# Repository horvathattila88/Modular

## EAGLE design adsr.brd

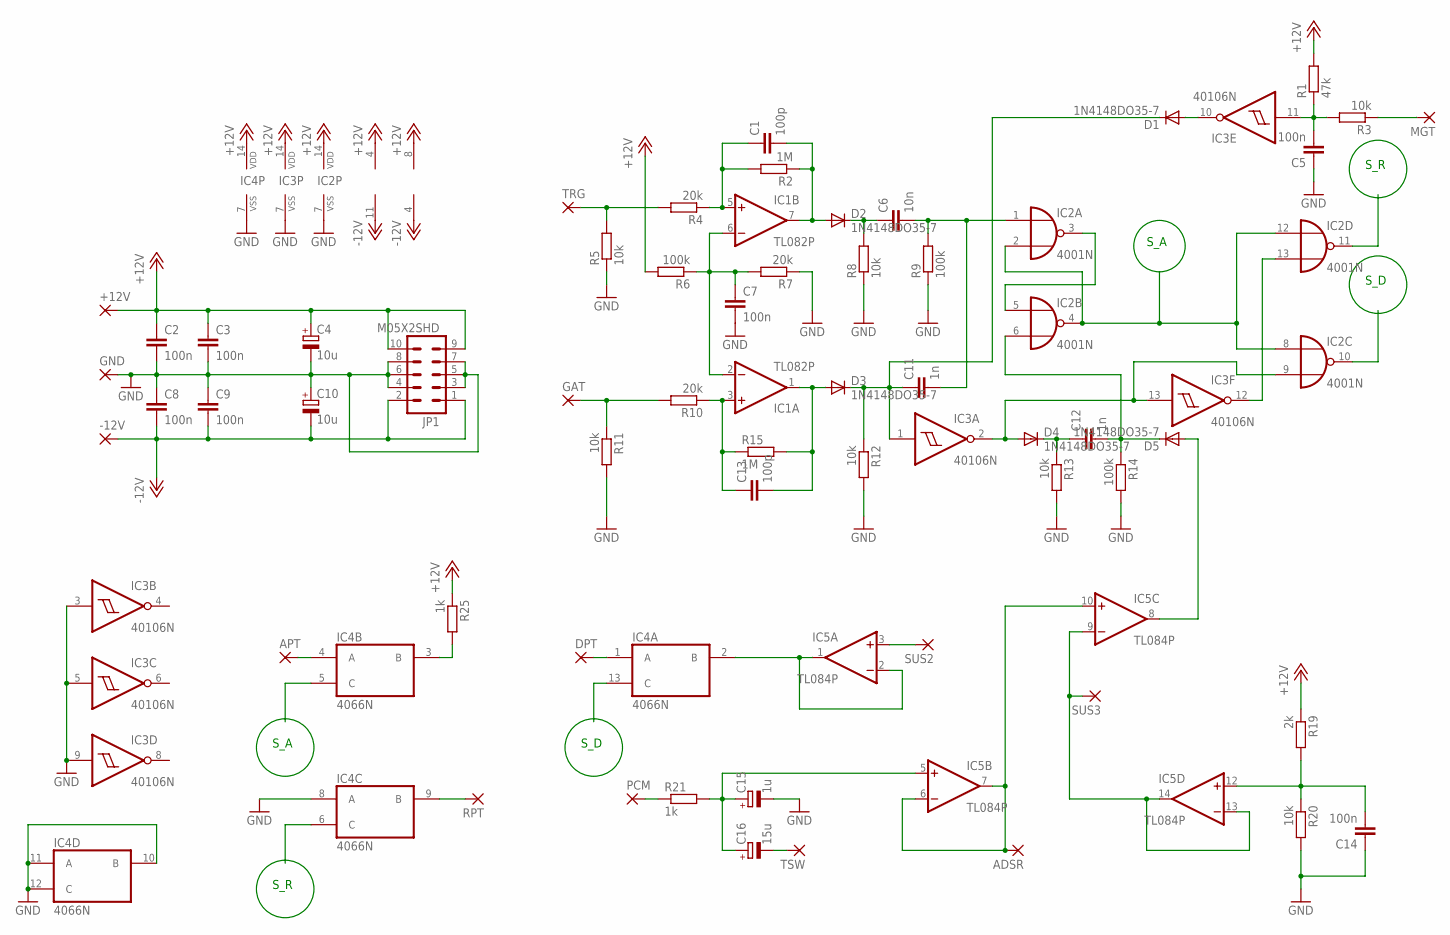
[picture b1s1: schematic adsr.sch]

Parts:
+12V: 2,54/1,0
-12V: 2,54/1,0
ADSR: 2,54/1,0
APT: 2,54/1,0
C1, C13: 100p; C050-035X075
C2, C3, C5, C7, C8, C9, C14: 100n; C050-035X075
C4, C10: 10u; E3,5-8
C6: 10n; C050-035X075
C11, C12: 1n; C050-035X075
C15: 1u; E2,5-6
C16: 15u; E3,5-8
D1, D2, D3, D4, D5: 1N4148DO35-7; DO35-7
DPT: 2,54/1,0
GAT: 2,54/1,0
GND: 2,54/1,0
IC1: TL082P; DIL08
IC2: 4001N; DIL14
IC3: 40106N; DIL14
IC4: 4066N; DIL14
IC5: TL084P; DIL14
JP1: M05X2SHD; 2X5-SHROUDED
MGT: 2,54/1,0
PCM: 2,54/1,0
R1: 47k; 0309/10
R2, R15: 1M; 0309/10
R3, R5, R8, R11, R12, R13, R20: 10k; 0309/10
R4, R7, R10: 20k; 0309/10
R6, R9, R14: 100k; 0309/10
R19: 2k; 0309/10
R21, R25: 1k; 0309/10
RPT: 2,54/1,0
SUS2, SUS3: 2,54/1,0
TRG: 2,54/1,0
TSW: 2,54/1,0

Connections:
+12V: +12V.1, C2.1, C3.1, C4.+, IC1.8 (V+), IC2.14 (VDD), IC3.14 (VDD), IC4.14 (VDD), IC5.4 (V+), JP1.9, JP1.10, R1.2, R6.2, R19.1, R25.1
-12V: -12V.1, C8.2, C9.2, C10.-, IC1.4 (V-), IC5.11 (V-), JP1.1, JP1.2
GND: C2.2, C3.2, C4.-, C5.1, C7.2, C8.1, C9.1, C10.+, C14.1, C15.-, GND.1, IC2.7 (VSS), IC3.3 (I), IC3.5 (I), IC3.7 (VSS), IC3.9 (I), IC4.7 (VSS), IC4.8 (A), IC4.10 (B), IC4.11 (A), IC4.12 (C), JP1.3, JP1.4, JP1.5, JP1.6, JP1.7, JP1.8, R5.1, R7.1, R8.1, R9.1, R11.2, R12.2, R13.2, R14.2, R20.2
unnamed: C1.1, IC1.5 (+IN), R2.2, R4.1
unnamed: R4.2, R5.2, TRG.1
unnamed: C1.2, D2.A, IC1.7 (OUT), R2.1
unnamed: C7.1, IC1.2 (-IN), IC1.6 (-IN), R6.1, R7.2
unnamed: C6.1, D2.C, R8.2
unnamed: C6.2, C11.2, IC2.1 (I0), R9.2
unnamed: C13.2, D3.A, IC1.1 (OUT), R15.2
unnamed: C13.1, IC1.3 (+IN), R10.1, R15.1
unnamed: GAT.1, R10.2, R11.1
unnamed: D4.A, IC2.9 (I1), IC3.2 (O), IC3.13 (I)
unnamed: IC2.3 (O), IC2.5 (I0)
unnamed: C11.1, D1.C, D3.C, IC3.1 (I), R12.1
unnamed: C12.1, D4.C, R13.1
unnamed: C12.2, D5.C, IC2.6 (I1), R14.1
unnamed: D5.A, IC5.8 (OUT)
unnamed: IC2.13 (I1), IC3.12 (O)
unnamed: C5.2, IC3.11 (I), R1.1, R3.2
unnamed: D1.A, IC3.10 (O)
unnamed: MGT.1, R3.1
unnamed: IC5.9 (-IN), IC5.13 (-IN), IC5.14 (OUT), SUS3.1
unnamed: ADSR.1, IC5.6 (-IN), IC5.7 (OUT), IC5.10 (+IN)
unnamed: IC5.3 (+IN), SUS2.1
unnamed: IC4.2 (B), IC5.1 (OUT), IC5.2 (-IN)
unnamed: DPT.1, IC4.1 (A)
unnamed: APT.1, IC4.4 (A)
unnamed: IC4.3 (B), R25.2
unnamed: IC4.9 (B), RPT.1
unnamed: PCM.1, R21.1
unnamed: C16.-, TSW.1
unnamed: C15.+, C16.+, IC5.5 (+IN), R21.2
unnamed: C14.2, IC5.12 (+IN), R19.2, R20.1
S_A: IC2.2 (I1), IC2.4 (O), IC2.8 (I0), IC2.12 (I0), IC4.5 (C)
S_D: IC2.10 (O), IC4.13 (C)
S_R: IC2.11 (O), IC4.6 (C)

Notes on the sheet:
S_A
S_D
S_R

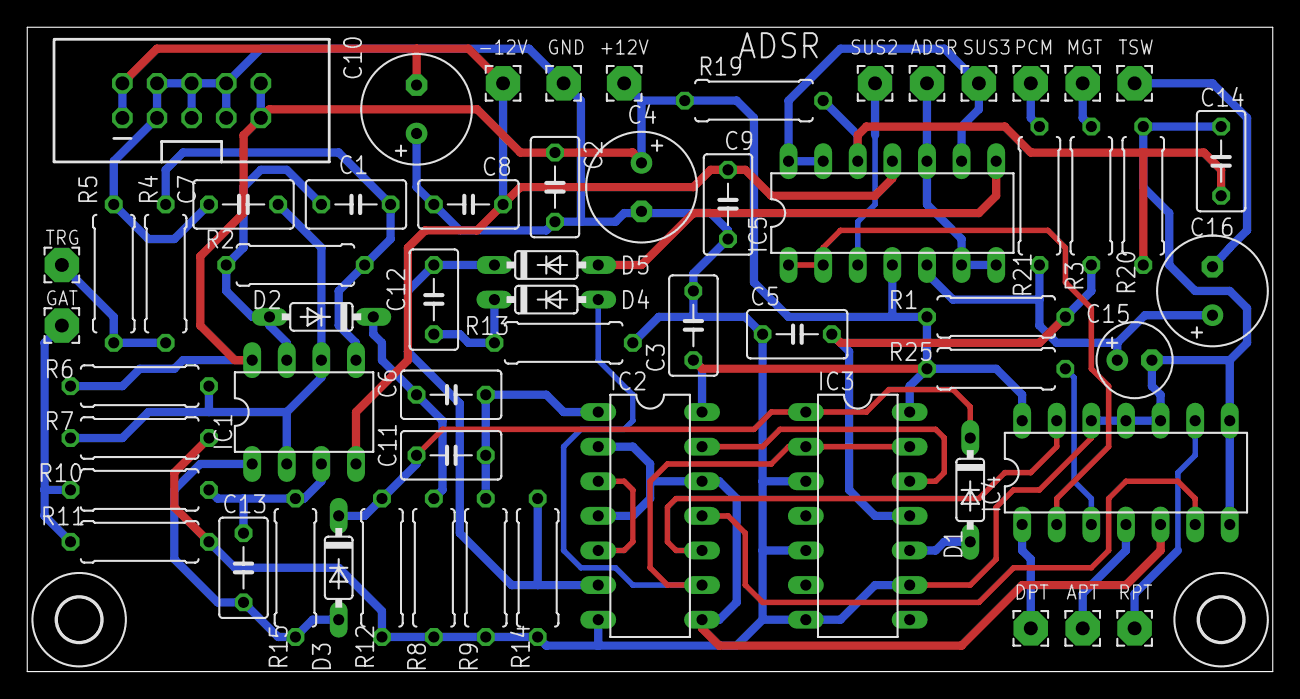
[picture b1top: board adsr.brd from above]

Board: 2 copper layers, 91.4 x 47.3 mm, 62 parts (0 on the bottom side), 37 nets.

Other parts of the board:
U$1, U$2: 3,2

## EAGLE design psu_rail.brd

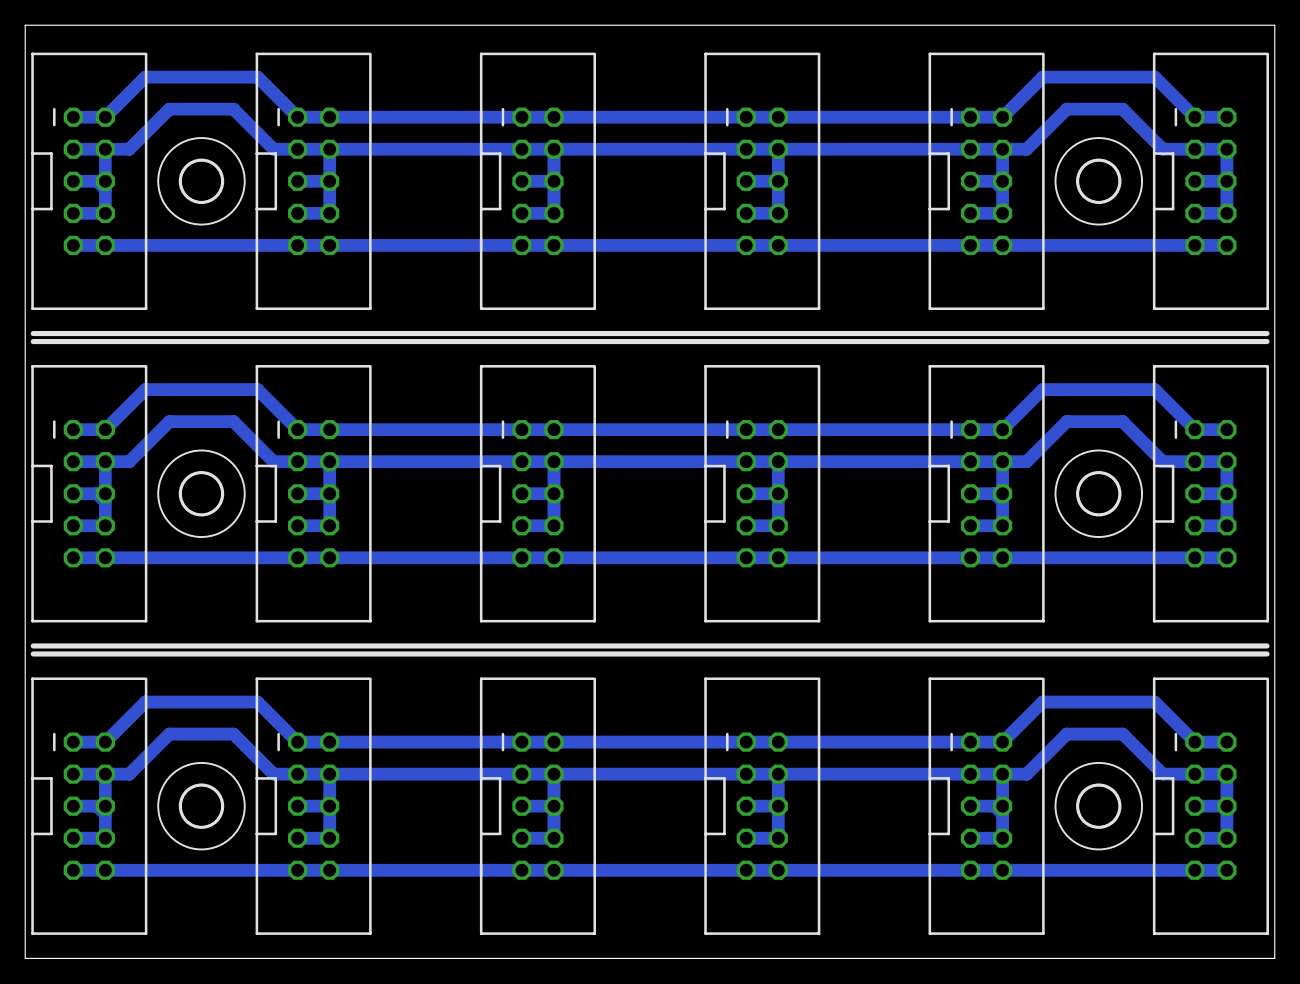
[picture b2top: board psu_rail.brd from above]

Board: 2 copper layers, 99.0 x 74.0 mm, 24 parts (0 on the bottom side), 9 nets.

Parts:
JP1, JP2, JP3, JP4, JP5, JP6, JP7, JP8, JP9, JP10, JP11, JP12, JP13, JP14, JP15, JP16, JP17, JP18: M05X2SHD; 2X5-SHROUDED
U$1, U$2, U$3, U$4, U$6, U$8: 3,2

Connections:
unnamed: JP1.1, JP1.2, JP2.1, JP2.2, JP3.1, JP3.2, JP4.1, JP4.2, JP11.1, JP11.2, JP12.1, JP12.2
unnamed: JP1.9, JP1.10, JP2.9, JP2.10, JP3.9, JP3.10, JP4.9, JP4.10, JP11.9, JP11.10, JP12.9, JP12.10
unnamed: JP1.3, JP1.4, JP1.5, JP1.6, JP1.7, JP1.8, JP2.3, JP2.4, JP2.5, JP2.6, JP2.7, JP2.8, JP3.3, JP3.4, JP3.5, JP3.6, JP3.7, JP3.8, JP4.3, JP4.4, JP4.5, JP4.6, JP4.7, JP4.8, JP11.3, JP11.4, JP11.5, JP11.6, JP11.7, JP11.8, JP12.3, JP12.4, JP12.5, JP12.6, JP12.7, JP12.8
unnamed: JP13.1, JP13.2, JP14.1, JP14.2, JP15.1, JP15.2, JP16.1, JP16.2, JP17.1, JP17.2, JP18.1, JP18.2
unnamed: JP13.9, JP13.10, JP14.9, JP14.10, JP15.9, JP15.10, JP16.9, JP16.10, JP17.9, JP17.10, JP18.9, JP18.10
unnamed: JP13.3, JP13.4, JP13.5, JP13.6, JP13.7, JP13.8, JP14.3, JP14.4, JP14.5, JP14.6, JP14.7, JP14.8, JP15.3, JP15.4, JP15.5, JP15.6, JP15.7, JP15.8, JP16.3, JP16.4, JP16.5, JP16.6, JP16.7, JP16.8, JP17.3, JP17.4, JP17.5, JP17.6, JP17.7, JP17.8, JP18.3, JP18.4, JP18.5, JP18.6, JP18.7, JP18.8
unnamed: JP5.1, JP5.2, JP6.1, JP6.2, JP7.1, JP7.2, JP8.1, JP8.2, JP9.1, JP9.2, JP10.1, JP10.2
unnamed: JP5.9, JP5.10, JP6.9, JP6.10, JP7.9, JP7.10, JP8.9, JP8.10, JP9.9, JP9.10, JP10.9, JP10.10
unnamed: JP5.3, JP5.4, JP5.5, JP5.6, JP5.7, JP5.8, JP6.3, JP6.4, JP6.5, JP6.6, JP6.7, JP6.8, JP7.3, JP7.4, JP7.5, JP7.6, JP7.7, JP7.8, JP8.3, JP8.4, JP8.5, JP8.6, JP8.7, JP8.8, JP9.3, JP9.4, JP9.5, JP9.6, JP9.7, JP9.8, JP10.3, JP10.4, JP10.5, JP10.6, JP10.7, JP10.8

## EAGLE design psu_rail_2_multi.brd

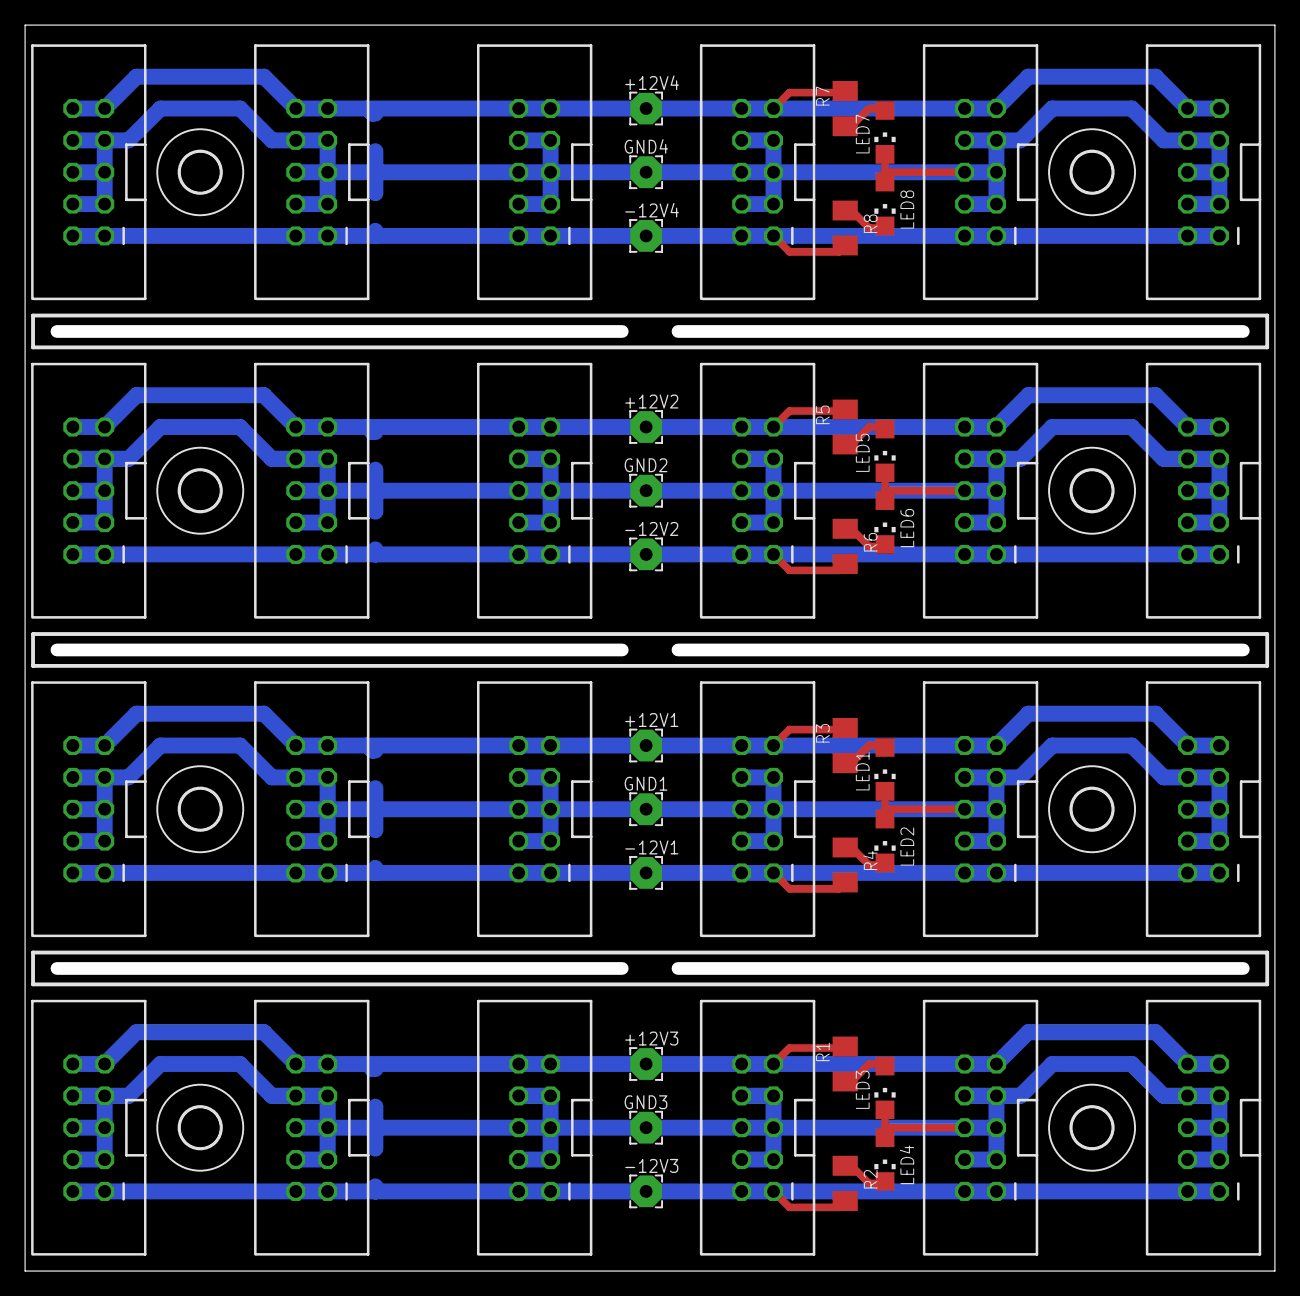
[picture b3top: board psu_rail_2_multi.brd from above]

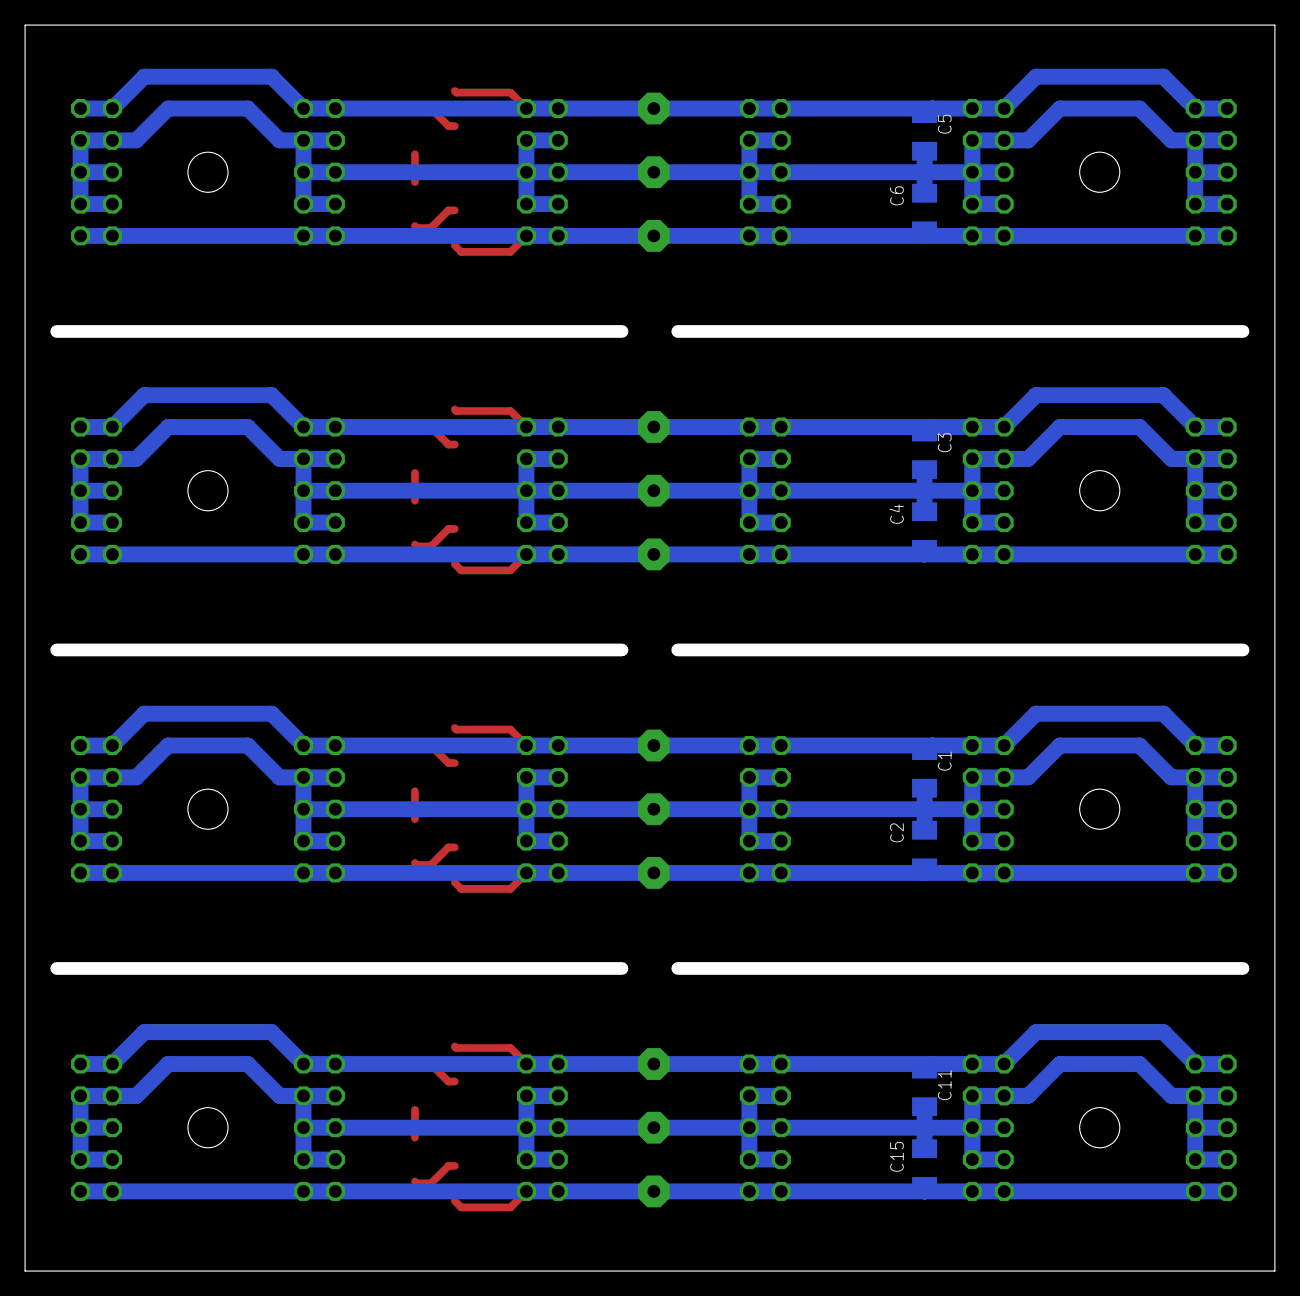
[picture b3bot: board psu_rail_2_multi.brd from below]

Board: 2 copper layers, 99.7 x 99.4 mm, 68 parts (8 on the bottom side), 20 nets.

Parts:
+12V1, +12V2, +12V3, +12V4: 2,54/1,0
-12V1, -12V2, -12V3, -12V4: 2,54/1,0
C1, C2, C3, C4, C5, C6, C11, C15: 100n; C1206K
GND1, GND2, GND3, GND4: 2,54/1,0
JP1, JP2, JP3, JP4, JP5, JP6, JP7, JP8, JP9, JP10, JP11, JP12, JP13, JP14, JP15, JP16, JP17, JP18, JP19, JP20, JP21, JP22, JP23, JP24: M05X2SHD; 2X5-SHROUDED
LED1, LED2, LED3, LED4, LED5, LED6, LED7, LED8: CHIPLED_1206
R1, R2, R3, R4, R5, R6, R7, R8: M1206
U$1, U$2, U$3, U$4, U$5, U$6, U$7, U$8: 3,2

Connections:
+12V: +12V3.1, C11.1, JP1.9, JP1.10, JP2.9, JP2.10, JP3.9, JP3.10, JP4.9, JP4.10, JP5.9, JP5.10, JP6.9, JP6.10, R1.2
+12V1: +12V1.1, C1.1, JP7.9, JP7.10, JP8.9, JP8.10, JP9.9, JP9.10, JP10.9, JP10.10, JP11.9, JP11.10, JP12.9, JP12.10, R3.2
+12V2: +12V2.1, C3.1, JP13.9, JP13.10, JP14.9, JP14.10, JP15.9, JP15.10, JP16.9, JP16.10, JP17.9, JP17.10, JP18.9, JP18.10, R5.2
+12V3: +12V4.1, C5.1, JP19.9, JP19.10, JP20.9, JP20.10, JP21.9, JP21.10, JP22.9, JP22.10, JP23.9, JP23.10, JP24.9, JP24.10, R7.2
-12V: -12V3.1, C15.2, JP1.1, JP1.2, JP2.1, JP2.2, JP3.1, JP3.2, JP4.1, JP4.2, JP5.1, JP5.2, JP6.1, JP6.2, R2.2
-12V1: -12V1.1, C2.2, JP7.1, JP7.2, JP8.1, JP8.2, JP9.1, JP9.2, JP10.1, JP10.2, JP11.1, JP11.2, JP12.1, JP12.2, R4.2
-12V2: -12V2.1, C4.2, JP13.1, JP13.2, JP14.1, JP14.2, JP15.1, JP15.2, JP16.1, JP16.2, JP17.1, JP17.2, JP18.1, JP18.2, R6.2
-12V3: -12V4.1, C6.2, JP19.1, JP19.2, JP20.1, JP20.2, JP21.1, JP21.2, JP22.1, JP22.2, JP23.1, JP23.2, JP24.1, JP24.2, R8.2
GND: C11.2, C15.1, GND3.1, JP1.3, JP1.4, JP1.5, JP1.6, JP1.7, JP1.8, JP2.3, JP2.4, JP2.5, JP2.6, JP2.7, JP2.8, JP3.3, JP3.4, JP3.5, JP3.6, JP3.7, JP3.8, JP4.3, JP4.4, JP4.5, JP4.6, JP4.7, JP4.8, JP5.3, JP5.4, JP5.5, JP5.6, JP5.7, JP5.8, JP6.3, JP6.4, JP6.5, JP6.6, JP6.7, JP6.8, LED3.C, LED4.A
GND1: C1.2, C2.1, GND1.1, JP7.3, JP7.4, JP7.5, JP7.6, JP7.7, JP7.8, JP8.3, JP8.4, JP8.5, JP8.6, JP8.7, JP8.8, JP9.3, JP9.4, JP9.5, JP9.6, JP9.7, JP9.8, JP10.3, JP10.4, JP10.5, JP10.6, JP10.7, JP10.8, JP11.3, JP11.4, JP11.5, JP11.6, JP11.7, JP11.8, JP12.3, JP12.4, JP12.5, JP12.6, JP12.7, JP12.8, LED1.C, LED2.A
GND2: C3.2, C4.1, GND2.1, JP13.3, JP13.4, JP13.5, JP13.6, JP13.7, JP13.8, JP14.3, JP14.4, JP14.5, JP14.6, JP14.7, JP14.8, JP15.3, JP15.4, JP15.5, JP15.6, JP15.7, JP15.8, JP16.3, JP16.4, JP16.5, JP16.6, JP16.7, JP16.8, JP17.3, JP17.4, JP17.5, JP17.6, JP17.7, JP17.8, JP18.3, JP18.4, JP18.5, JP18.6, JP18.7, JP18.8, LED5.C, LED6.A
GND3: C5.2, C6.1, GND4.1, JP19.3, JP19.4, JP19.5, JP19.6, JP19.7, JP19.8, JP20.3, JP20.4, JP20.5, JP20.6, JP20.7, JP20.8, JP21.3, JP21.4, JP21.5, JP21.6, JP21.7, JP21.8, JP22.3, JP22.4, JP22.5, JP22.6, JP22.7, JP22.8, JP23.3, JP23.4, JP23.5, JP23.6, JP23.7, JP23.8, JP24.3, JP24.4, JP24.5, JP24.6, JP24.7, JP24.8, LED7.C, LED8.A
unnamed: LED4.C, R2.1
unnamed: LED3.A, R1.1
unnamed: LED2.C, R4.1
unnamed: LED1.A, R3.1
unnamed: LED6.C, R6.1
unnamed: LED5.A, R5.1
unnamed: LED8.C, R8.1
unnamed: LED7.A, R7.1

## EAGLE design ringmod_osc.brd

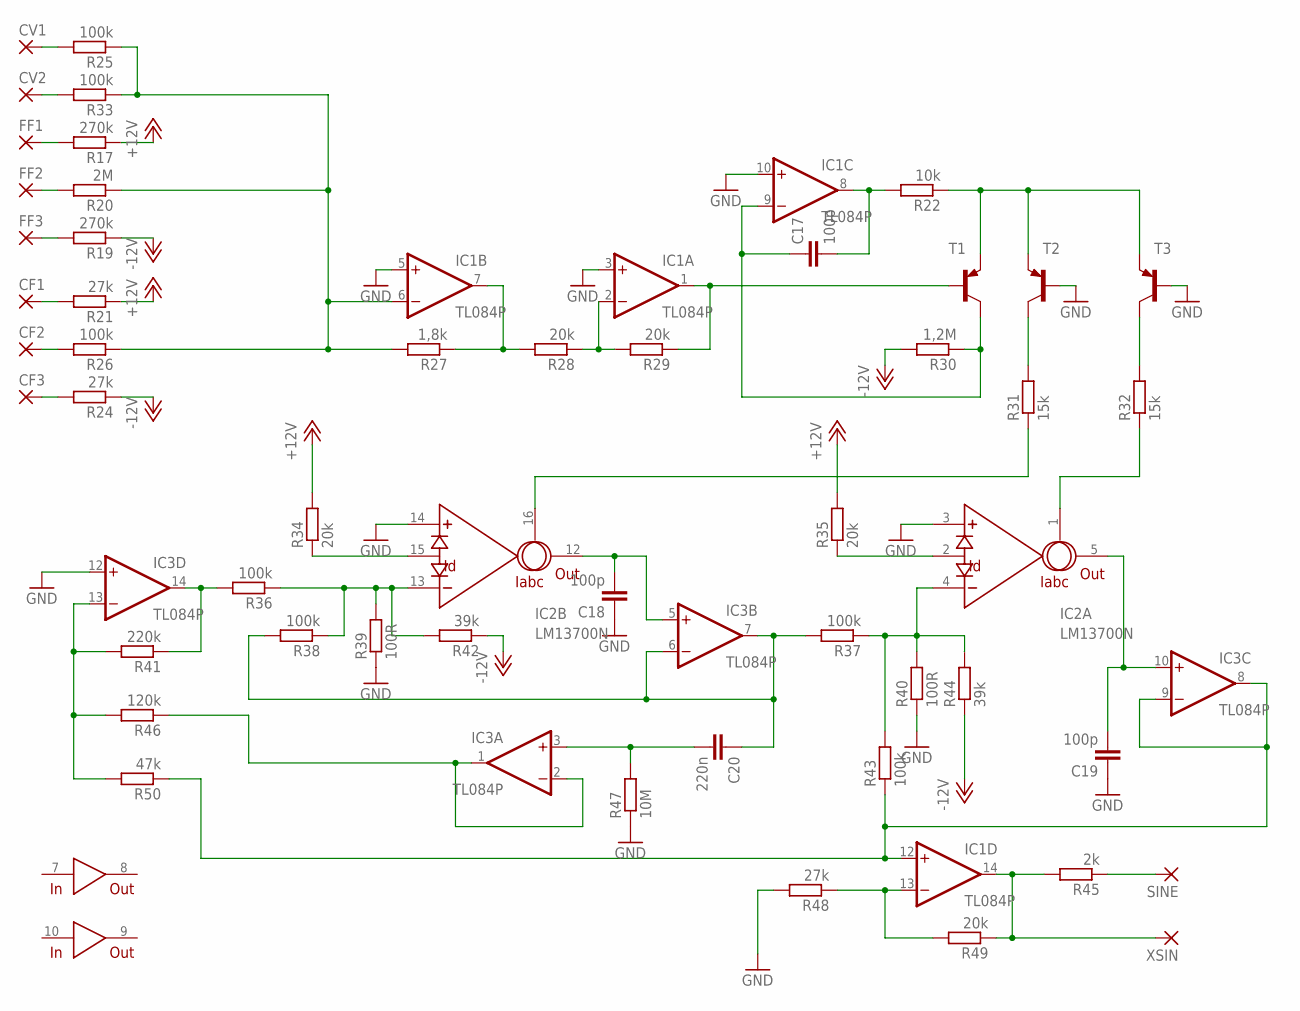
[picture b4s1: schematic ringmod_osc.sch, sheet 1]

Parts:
C17, C18, C19: 100p; C050-035X075
C20: 220n; C050-035X075
CF1, CF2, CF3: 2,54/1,0
CV1, CV2: 2,54/1,0
FF1, FF2, FF3: 2,54/1,0
IC1, IC3: TL084P; DIL14
IC2: LM13700N; DIL16
R17, R19: 270k; 0309V
R20: 2M; 0309V
R21, R24: 27k; 0309V
R22: 10k; 0309/10
R25, R26, R33: 100k; 0309V
R27: 1,8k; 0309/10
R28, R29, R34, R35, R49: 20k; 0309/10
R30: 1,2M; 0309/10
R31, R32: 15k; 0309/10
R36, R37, R38, R43: 100k; 0309/10
R39, R40: 100R; 0309/10
R41: 220k; 0309/10
R42, R44: 39k; 0309/10
R45: 2k; 0309/10
R46: 120k; 0309/10
R47: 10M; 0309/10
R48: 27k; 0309/10
R50: 47k; 0309/10
SINE: 2,54/1,0
T1, T2, T3: 2N3906-PNP-TO92-EBC; TO92-EBC
XSIN: 2,54/1,0

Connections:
+12V: R17.1, R21.1, R34.2, R35.2; also elsewhere on the board
-12V: R19.1, R24.1, R30.2, R42.1, R44.1; also elsewhere on the board
GND: C18.1, C19.1, IC1.3 (+IN), IC1.5 (+IN), IC1.10 (+IN), IC2.3 (+IN), IC2.14 (+IN), IC3.12 (+IN), R39.1, R40.1, R47.1, R48.2, T2.B, T3.B; also elsewhere on the board
unnamed: FF1.1, R17.2
unnamed: FF3.1, R19.2
unnamed: FF2.1, R20.2
unnamed: CF1.1, R21.2
unnamed: CF2.1, R26.2
unnamed: CF3.1, R24.2
unnamed: C20.2, IC3.3 (+IN), R47.2
unnamed: CV1.1, R25.2
unnamed: CV2.1, R33.2
unnamed: IC1.6 (-IN), R20.1, R25.1, R26.1, R27.2, R33.1
unnamed: IC1.7 (OUT), R27.1, R28.2
unnamed: IC1.2 (-IN), R28.1, R29.2
unnamed: IC1.1 (OUT), R29.1, T1.B
unnamed: C17.2, IC1.8 (OUT), R22.2
unnamed: R31.2, T2.C
unnamed: R32.2, T3.C
unnamed: C17.1, IC1.9 (-IN), R30.1, T1.C
unnamed: R22.1, T1.E, T2.E, T3.E
unnamed: IC2.1 (IABC), R32.1
unnamed: IC2.16 (IABC), R31.1
unnamed: IC2.15 (ID), R34.1
unnamed: IC2.2 (ID), R35.1
unnamed: IC2.13 (-IN), R36.1, R38.1, R39.2, R42.2
unnamed: IC3.14 (OUT), R36.2, R41.1
unnamed: IC3.13 (-IN), R41.2, R46.2, R50.2
unnamed: C20.1, IC3.6 (-IN), IC3.7 (OUT), R37.2, R38.2
unnamed: C18.2, IC2.12 (OUT), IC3.5 (+IN)
unnamed: IC3.1 (OUT), IC3.2 (-IN), R46.1
unnamed: IC2.4 (-IN), R37.1, R40.2, R43.2, R44.2
unnamed: IC1.12 (+IN), IC3.8 (OUT), IC3.9 (-IN), R43.1, R50.1
unnamed: IC1.13 (-IN), R48.1, R49.2
unnamed: IC1.14 (OUT), R45.2, R49.1, XSIN.1
unnamed: R45.1, SINE.1
unnamed: C19.2, IC2.5 (OUT), IC3.10 (+IN)

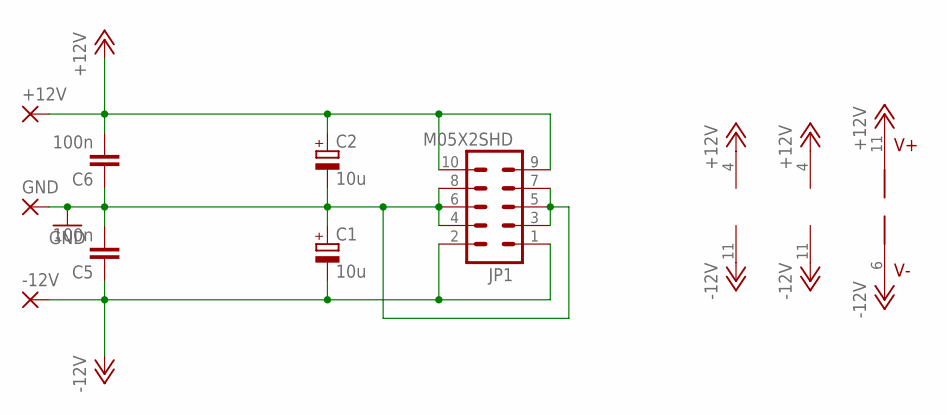
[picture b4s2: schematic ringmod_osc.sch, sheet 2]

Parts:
+12V: 2,54/1,0
-12V: 2,54/1,0
C1, C2: 10u; E3,5-8
C5, C6: 100n; C050-035X075
GND: 2,54/1,0
IC1, IC3: TL084P; DIL14
IC2: LM13700N; DIL16
JP1: M05X2SHD; 2X5-SHROUDED

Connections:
+12V: +12V.1, C2.+, C6.2, IC1.4 (V+), IC2.11 (V+), IC3.4 (V+), JP1.9, JP1.10; also elsewhere on the board
-12V: -12V.1, C1.-, C5.1, IC1.11 (V-), IC2.6 (V-), IC3.11 (V-), JP1.1, JP1.2; also elsewhere on the board
GND: C1.+, C2.-, C5.2, C6.1, GND.1, JP1.3, JP1.4, JP1.5, JP1.6, JP1.7, JP1.8; also elsewhere on the board

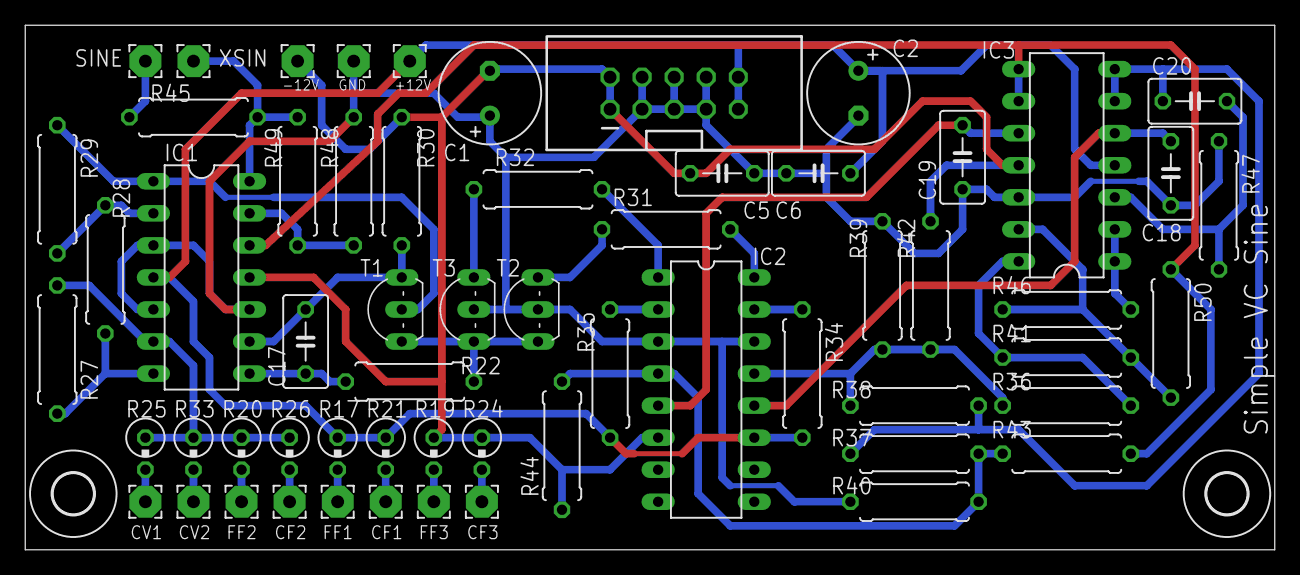
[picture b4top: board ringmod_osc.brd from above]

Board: 2 copper layers, 99.0 x 41.6 mm, 62 parts (0 on the bottom side), 37 nets.

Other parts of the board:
U$1, U$2: 3,2

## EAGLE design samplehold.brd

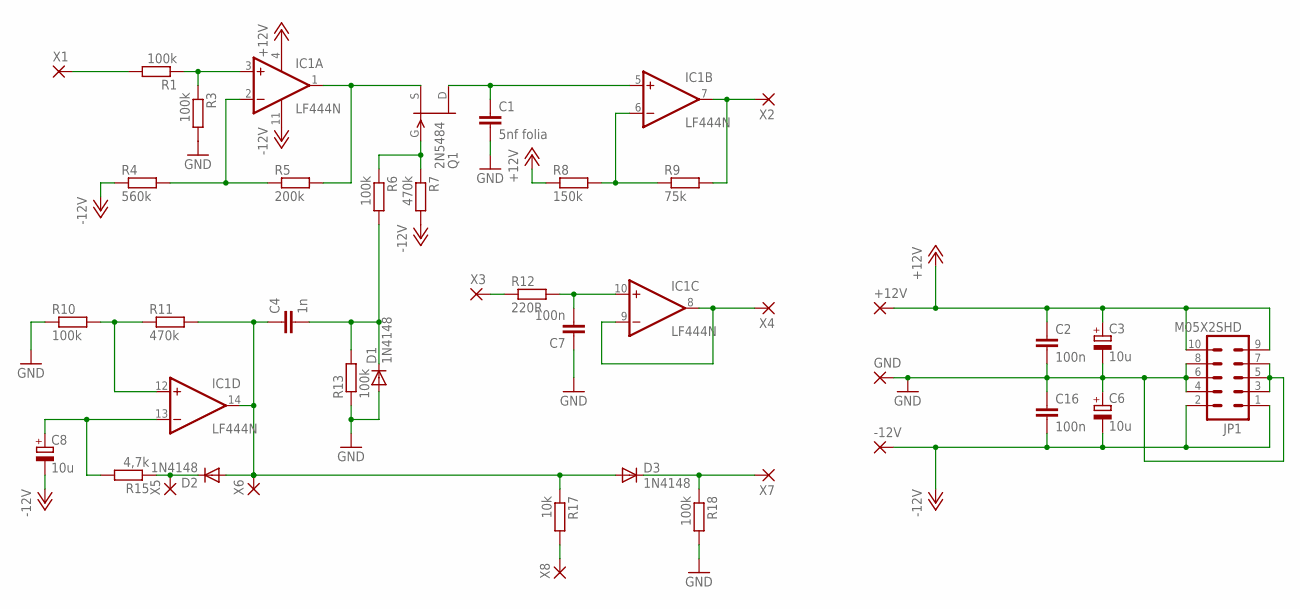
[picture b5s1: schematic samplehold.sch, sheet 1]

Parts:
+12V: 2,54/1,0
-12V: 2,54/1,0
C1: 5nf folia; C050-035X075
C2, C7, C16: 100n; C050-035X075
C3, C6: 10u; E3,5-8
C4: 1n; C050-035X075
C8: 10u; E2,5-7
D1, D2, D3: 1N4148; DO35-7
GND: 2,54/1,0
IC1: LF444N; DIL14
JP1: M05X2SHD; 2X5-SHROUDED
Q1: 2N5484; TO92-
R1, R3, R6, R10, R13, R18: 100k; 0309/10
R4: 560k; 0309/10
R5: 200k; 0309/10
R7, R11: 470k; 0309/10
R8: 150k; 0309/10
R9: 75k; 0309/10
R12: 220R; 0309/10
R15: 4,7k; 0309/10
R17: 10k; 0309/10
X1, X2, X3, X4, X5, X6, X7, X8: 2,54/1,0

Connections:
+12V: +12V.1, C2.1, C3.+, IC1.4 (V+), JP1.9, JP1.10, R8.1; also elsewhere on the board
-12V: -12V.1, C6.-, C8.-, C16.2, IC1.11 (V-), JP1.1, JP1.2, R4.1, R7.2; also elsewhere on the board
GND: C1.2, C2.2, C3.-, C6.+, C7.1, C16.1, D1.A, GND.1, JP1.3, JP1.4, JP1.5, JP1.6, JP1.7, JP1.8, R3.2, R10.1, R13.1, R18.2; also elsewhere on the board
unnamed: IC1.3 (+IN), R1.1, R3.1
unnamed: R1.2, X1.1
unnamed: IC1.1 (OUT), Q1.2 (S), R5.2
unnamed: IC1.2 (-IN), R4.2, R5.1
unnamed: C1.1, IC1.5 (+IN), Q1.3 (D)
unnamed: Q1.1 (G), R6.1, R7.1
unnamed: IC1.12 (+IN), R10.2, R11.1
unnamed: C4.2, D1.C, R6.2, R13.2
unnamed: IC1.6 (-IN), R8.2, R9.1
unnamed: IC1.7 (OUT), R9.2, X2.1
unnamed: C4.1, D2.A, D3.A, IC1.14 (OUT), R11.2, R17.1, X6.1
unnamed: C8.+, IC1.13 (-IN), R15.2
unnamed: D2.C, R15.1, X5.1
unnamed: R17.2, X8.1
unnamed: D3.C, R18.1, X7.1
unnamed: C7.2, IC1.10 (+IN), R12.2
unnamed: R12.1, X3.1
unnamed: IC1.8 (OUT), IC1.9 (-IN), X4.1

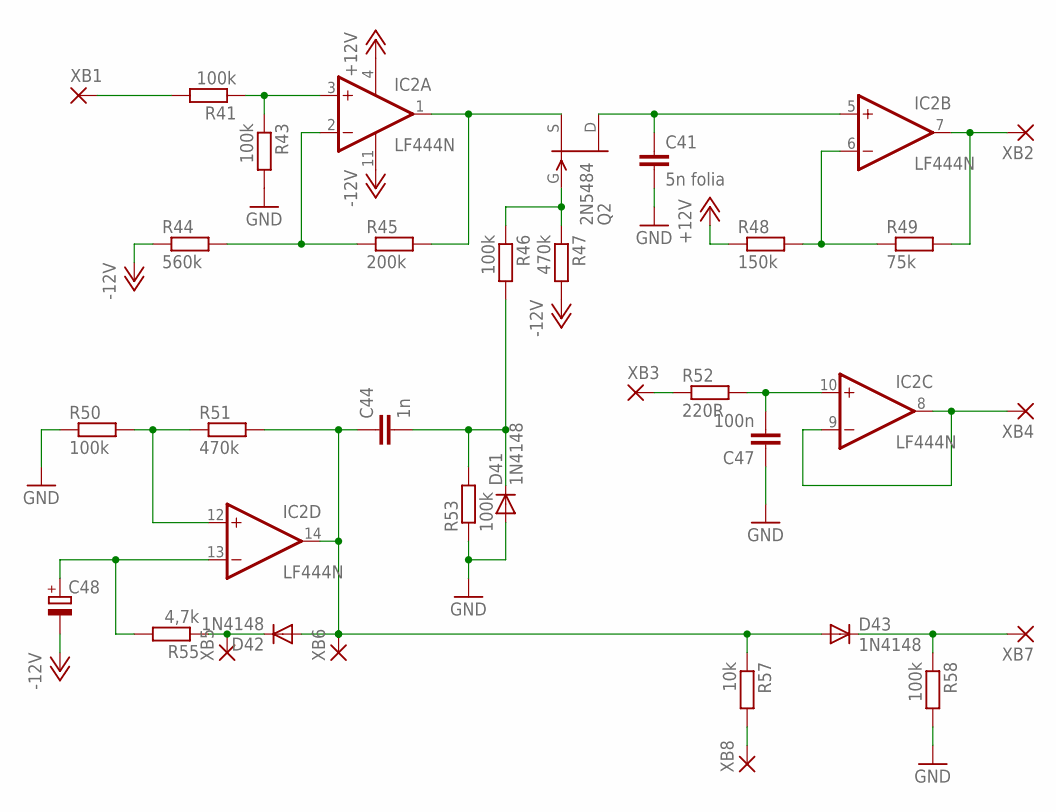
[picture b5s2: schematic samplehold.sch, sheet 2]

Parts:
C41: 5n folia; C050-035X075
C44: 1n; C050-035X075
C47: 100n; C050-035X075
C48: CPOL-EUE2.5-7; E2,5-7
D41, D42, D43: 1N4148; DO35-7
IC2: LF444N; DIL14
Q2: 2N5484; TO92-
R41, R43, R46, R50, R53, R58: 100k; 0309/10
R44: 560k; 0309/10
R45: 200k; 0309/10
R47, R51: 470k; 0309/10
R48: 150k; 0309/10
R49: 75k; 0309/10
R52: 220R; 0309/10
R55: 4,7k; 0309/10
R57: 10k; 0309/10
XB1, XB2, XB3, XB4, XB5, XB6, XB7, XB8: 2,54/1,0

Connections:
+12V: IC2.4 (V+), R48.1; also elsewhere on the board
-12V: C48.-, IC2.11 (V-), R44.1, R47.2; also elsewhere on the board
GND: C41.2, C47.1, D41.A, R43.2, R50.1, R53.1, R58.2; also elsewhere on the board
unnamed: IC2.3 (+IN), R41.1, R43.1
unnamed: R41.2, XB1.1
unnamed: IC2.1 (OUT), Q2.2 (S), R45.2
unnamed: IC2.2 (-IN), R44.2, R45.1
unnamed: C41.1, IC2.5 (+IN), Q2.3 (D)
unnamed: Q2.1 (G), R46.1, R47.1
unnamed: C44.2, D41.C, R46.2, R53.2
unnamed: IC2.6 (-IN), R48.2, R49.1
unnamed: IC2.7 (OUT), R49.2, XB2.1
unnamed: IC2.12 (+IN), R50.2, R51.1
unnamed: C44.1, D42.A, D43.A, IC2.14 (OUT), R51.2, R57.1, XB6.1
unnamed: C48.+, IC2.13 (-IN), R55.2
unnamed: D42.C, R55.1, XB5.1
unnamed: R57.2, XB8.1
unnamed: D43.C, R58.1, XB7.1
unnamed: C47.2, IC2.10 (+IN), R52.2
unnamed: R52.1, XB3.1
unnamed: IC2.8 (OUT), IC2.9 (-IN), XB4.1

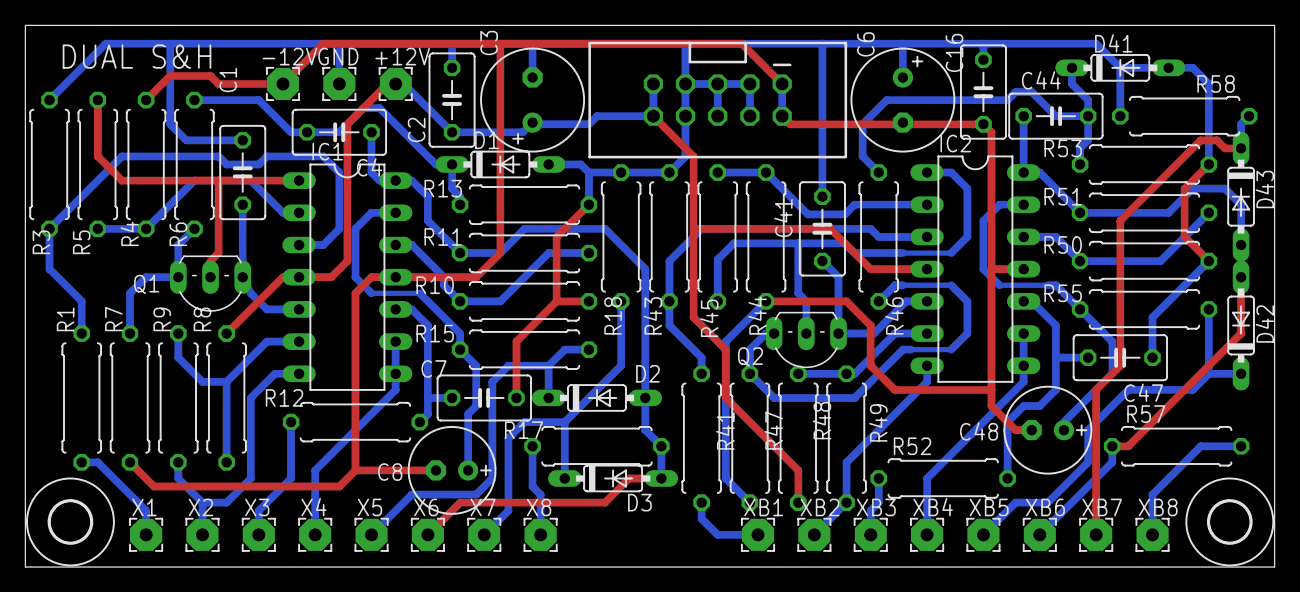
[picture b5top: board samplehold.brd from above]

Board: 2 copper layers, 98.5 x 42.7 mm, 74 parts (0 on the bottom side), 39 nets.

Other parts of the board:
U$1, U$2: 3,2

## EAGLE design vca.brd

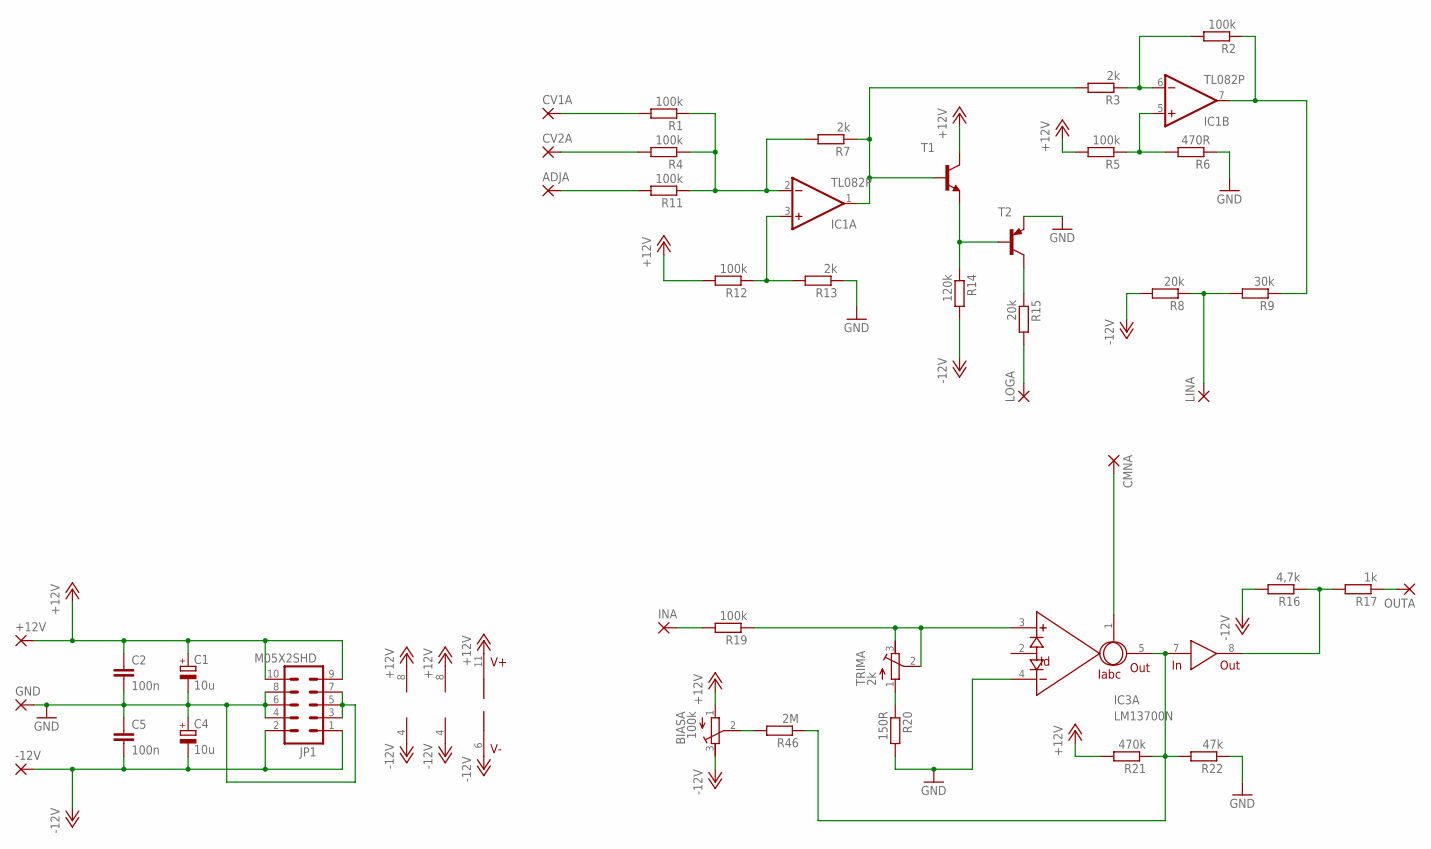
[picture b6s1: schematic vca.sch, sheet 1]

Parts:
+12V: 2,54/1,0
-12V: 2,54/1,0
ADJA: 2,54/1,0
BIASA: 100k; RTRIM64W
C1, C4: 10u; E3,5-8
C2, C5: 100n; C050-035X075
CMNA: 2,54/1,0
CV1A, CV2A: 2,54/1,0
GND: 2,54/1,0
IC1, IC2: TL082P; DIL08
IC3: LM13700N; DIL16
INA: 2,54/1,0
JP1: M05X2SHD; 2X5-SHROUDED
LINA: 2,54/1,0
LOGA: 2,54/1,0
OUTA: 2,54/1,0
R1, R4, R11: 100k; 0309V
R2, R5, R12, R19: 100k; 0309/10
R3, R13: 2k; 0309/10
R6: 470R; 0309/10
R7: 2k; 0309V
R8: 20k; 0309/10
R9: 30k; 0309V
R14: 120k; 0309/10
R15: 20k; 0309V
R16: 4,7k; 0309/10
R17: 1k; 0309/10
R20: 150R; 0309/10
R21: 470k; 0309/10
R22: 47k; 0309/10
R46: 2M; 0309/10
T1: 2N3904-NPN-TO92-EBC; TO92-EBC
T2: 2N3906-PNP-TO92-EBC; TO92-EBC
TRIMA: 2k; RTRIM64W

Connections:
+12V: +12V.1, BIASA.1 (A), C1.+, C2.1, IC1.8 (V+), IC2.8 (V+), IC3.11 (V+), JP1.9, JP1.10, R5.2, R12.2, R21.2, T1.C; also elsewhere on the board
-12V: -12V.1, BIASA.3 (E), C4.-, C5.2, IC1.4 (V-), IC2.4 (V-), IC3.6 (V-), JP1.1, JP1.2, R8.2, R14.2, R16.2; also elsewhere on the board
GND: C1.-, C2.2, C4.+, C5.1, GND.1, IC3.4 (-IN), JP1.3, JP1.4, JP1.5, JP1.6, JP1.7, JP1.8, R6.1, R13.1, R20.2, R22.1, T2.E; also elsewhere on the board
unnamed: CV1A.1, R1.2
unnamed: CV2A.1, R4.2
unnamed: ADJA.1, R11.2
unnamed: IC1.2 (-IN), R1.1, R4.1, R7.2, R11.1
unnamed: IC1.3 (+IN), R12.1, R13.2
unnamed: IC1.1 (OUT), R3.2, R7.1, T1.B
unnamed: R14.1, T1.E, T2.B
unnamed: R15.1, T2.C
unnamed: LOGA.1, R15.2
unnamed: IC1.6 (-IN), R2.2, R3.1
unnamed: IC1.7 (OUT), R2.1, R9.1
unnamed: IC1.5 (+IN), R5.1, R6.2
unnamed: LINA.1, R8.1, R9.2
unnamed: IC3.5 (OUT), IC3.7 (IN), R21.1, R22.2, R46.1
unnamed: INA.1, R19.2
unnamed: CMNA.1, IC3.1 (IABC)
unnamed: IC3.3 (+IN), R19.1, TRIMA.2 (S), TRIMA.3 (E)
unnamed: R20.1, TRIMA.1 (A)
unnamed: OUTA.1, R17.1
unnamed: BIASA.2 (S), R46.2
unnamed: IC3.8 (OUT), R16.1, R17.2
